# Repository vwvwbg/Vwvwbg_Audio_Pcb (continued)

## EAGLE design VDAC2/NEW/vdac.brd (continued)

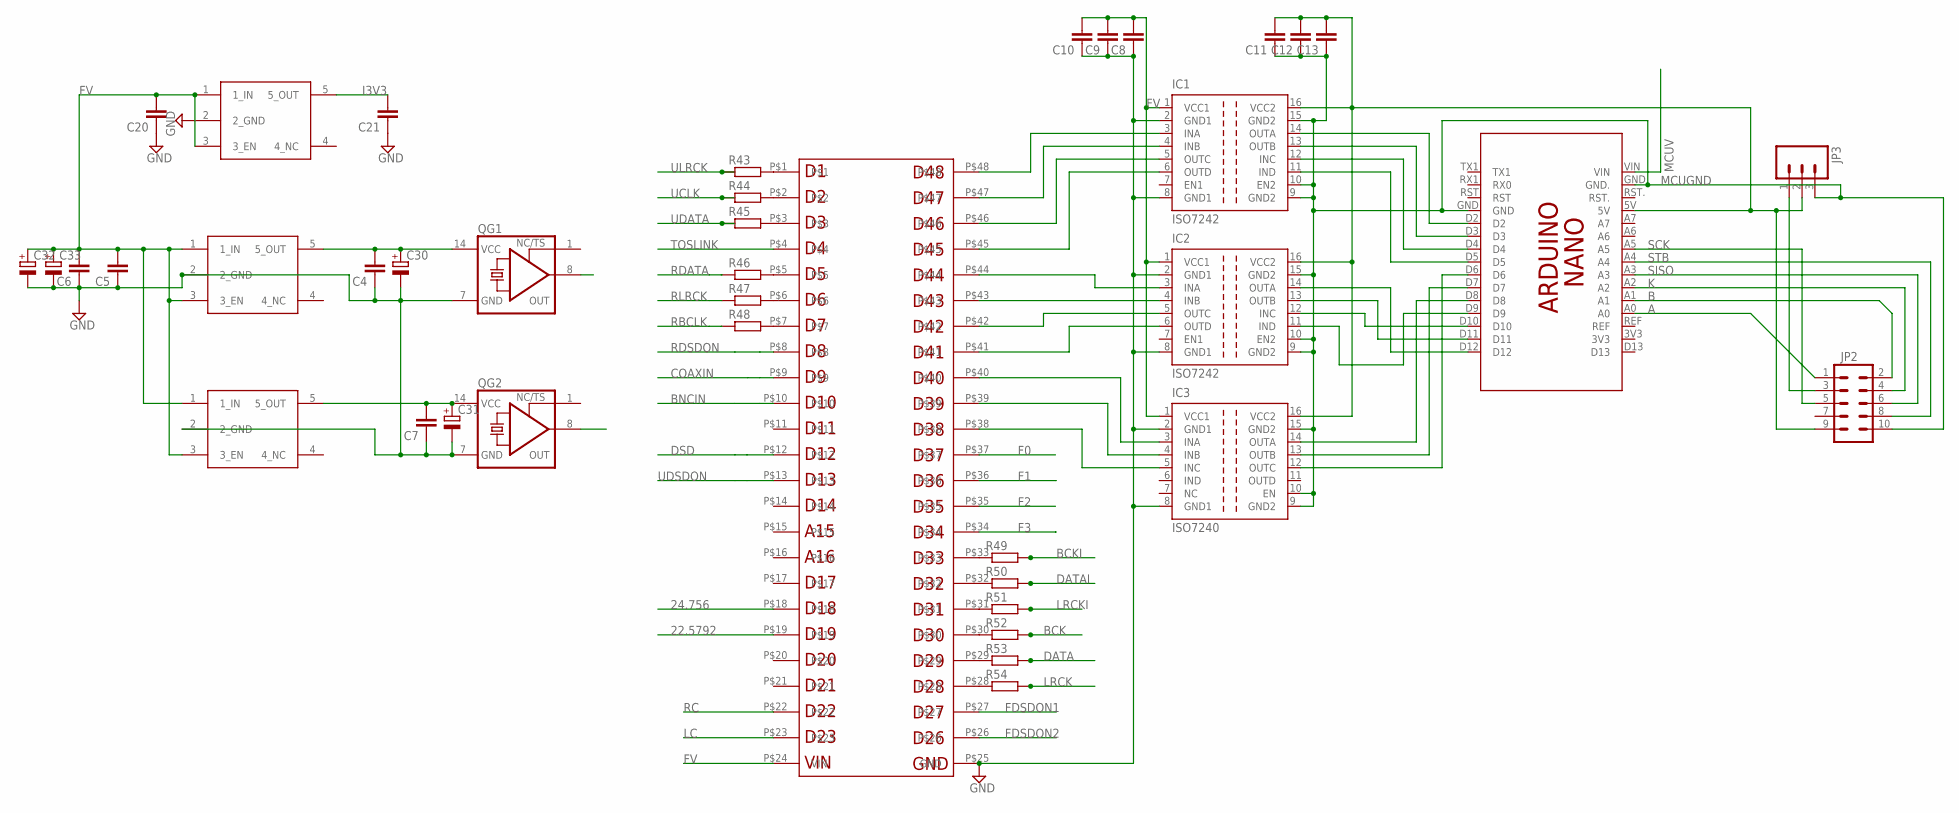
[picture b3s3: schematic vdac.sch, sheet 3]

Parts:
C4, C5, C6, C7, C8, C9, C10, C11, C12, C13, C20, C21: C-EUC0805; C0805
C30, C31, C32, C33: CPOL-EUSP-CAP-CX; SP-CAP-CX
IC1, IC2: ISO7242; SO-16DW
IC3: ISO7240; SO-16DW
JP2: M05X2SHD; 2X5-SHROUDED
JP3: M03JST-PTH-VERT; JST-3-PTH-VERT
PCB1: ARDUINO_NANO
QG1, QG2: XO-14; DIL14S
R43, R44, R45, R46, R47, R48, R49, R50, R51, R52, R53, R54: R-EU_MELF0204W; MINI_MELF-0204W
U$10, U$15, U$16: LP5907; SOT-23-5
U$12: CMOD-A7; CMODA7

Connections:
22.5792: QG2.8 (OUT), U$12.P$19
24.756: QG1.8 (OUT), U$12.P$18
A: JP2.1, PCB1.A0
B: JP2.2, PCB1.A1
BCK: R52.2
BCKI: R49.2; also elsewhere on the board
BNCIN: U$12.P$10; also elsewhere on the board
COAXIN: U$12.P$9; also elsewhere on the board
D2: IC1.14 (OUTA), PCB1.D2
D3: IC1.13 (OUTB), PCB1.D3
D4: IC1.12 (INC), PCB1.D4
D5: IC1.11 (IND), PCB1.D5
DATA: R53.2
DATAI: R50.2; also elsewhere on the board
DSD: U$12.P$12; also elsewhere on the board
F0: U$12.P$37; also elsewhere on the board
F1: U$12.P$36; also elsewhere on the board
F2: U$12.P$35; also elsewhere on the board
F3: U$12.P$34; also elsewhere on the board
FDSDON1: U$12.P$27
FDSDON2: U$12.P$26
FV: C5.2, C6.2, C8.2, C9.2, C10.2, C20.2, C32.+, C33.+, IC1.1 (VCC1), IC2.1 (VCC1), IC3.1 (VCC1), U$10.1 (1_IN), U$10.3 (3_EN), U$12.P$24 (VIN), U$15.1 (1_IN), U$15.3 (3_EN), U$16.1 (1_IN), U$16.3 (3_EN); also elsewhere on the board
GND: C4.1, C5.1, C6.1, C7.1, C8.1, C9.1, C10.1, C20.1, C21.1, C30.-, C31.-, C32.-, C33.-, IC1.2 (GND1), IC1.8 (GND1), IC2.2 (GND1), IC2.8 (GND1), IC3.2 (GND1), IC3.8 (GND1), QG1.7 (GND), QG2.7 (GND), U$10.2 (2_GND), U$12.P$25 (GND), U$15.2 (2_GND), U$16.2 (2_GND); also elsewhere on the board
I3V3: C21.2, U$10.5 (5_OUT); also elsewhere on the board
K: JP2.4, PCB1.A2
LC: U$12.P$23
LRCK: R54.2
LRCKI: R51.2; also elsewhere on the board
MCUGND: C11.1, C12.1, C13.1, IC1.9 (GND2), IC1.10 (EN2), IC1.15 (GND2), IC2.9 (GND2), IC2.10 (EN2), IC2.15 (GND2), IC3.9 (GND2), IC3.10 (EN), IC3.15 (GND2), JP2.10, JP3.3, PCB1.GND, PCB1.GND.; also elsewhere on the board
MCUV: PCB1.VIN; also elsewhere on the board
unnamed: R43.2, U$12.P$1
unnamed: C4.2, C30.+, QG1.14 (VCC), U$15.5 (5_OUT)
unnamed: C7.2, C31.+, QG2.14 (VCC), U$16.5 (5_OUT)
unnamed: IC1.3 (INA), U$12.P$48
unnamed: IC1.4 (INB), U$12.P$47
unnamed: IC1.5 (OUTC), U$12.P$46
unnamed: IC1.6 (OUTD), U$12.P$45
unnamed: IC2.3 (INA), U$12.P$44
unnamed: IC2.4 (INB), U$12.P$43
unnamed: IC2.5 (OUTC), U$12.P$42
unnamed: IC2.6 (OUTD), U$12.P$41
unnamed: IC3.3 (INA), U$12.P$40
unnamed: IC3.4 (INB), U$12.P$39
unnamed: IC3.5 (INC), U$12.P$38
unnamed: IC2.14 (OUTA), PCB1.D12
unnamed: IC2.13 (OUTB), PCB1.D11
unnamed: IC2.12 (INC), PCB1.D10
unnamed: IC2.11 (IND), PCB1.D9
unnamed: IC3.14 (OUTA), PCB1.D8
unnamed: IC3.13 (OUTB), PCB1.D7
unnamed: IC3.12 (OUTC), PCB1.D6
unnamed: C11.2, C12.2, C13.2, IC1.16 (VCC2), IC2.16 (VCC2), IC3.16 (VCC2), JP2.9, JP3.2, PCB1.5V
unnamed: JP2.3, JP3.1
unnamed: R44.2, U$12.P$2
unnamed: R45.2, U$12.P$3
unnamed: R46.2, U$12.P$5
unnamed: R47.2, U$12.P$6
unnamed: R48.2, U$12.P$7
unnamed: R49.1, U$12.P$33
unnamed: R50.1, U$12.P$32
unnamed: R51.1, U$12.P$31
unnamed: R52.1, U$12.P$30
unnamed: R53.1, U$12.P$29
unnamed: R54.1, U$12.P$28
RBCLK: R48.1; also elsewhere on the board
RC: U$12.P$22
RDATA: R46.1; also elsewhere on the board
RDSDON: U$12.P$8; also elsewhere on the board
RLRCK: R47.1; also elsewhere on the board
SCK: JP2.5, PCB1.A5
SISO: JP2.6, PCB1.A3
STB: JP2.8, PCB1.A4
TOSLINK: U$12.P$4; also elsewhere on the board
UCLK: R44.1; also elsewhere on the board
UDATA: R45.1; also elsewhere on the board
UDSDON: U$12.P$13; also elsewhere on the board
ULRCK: R43.1; also elsewhere on the board

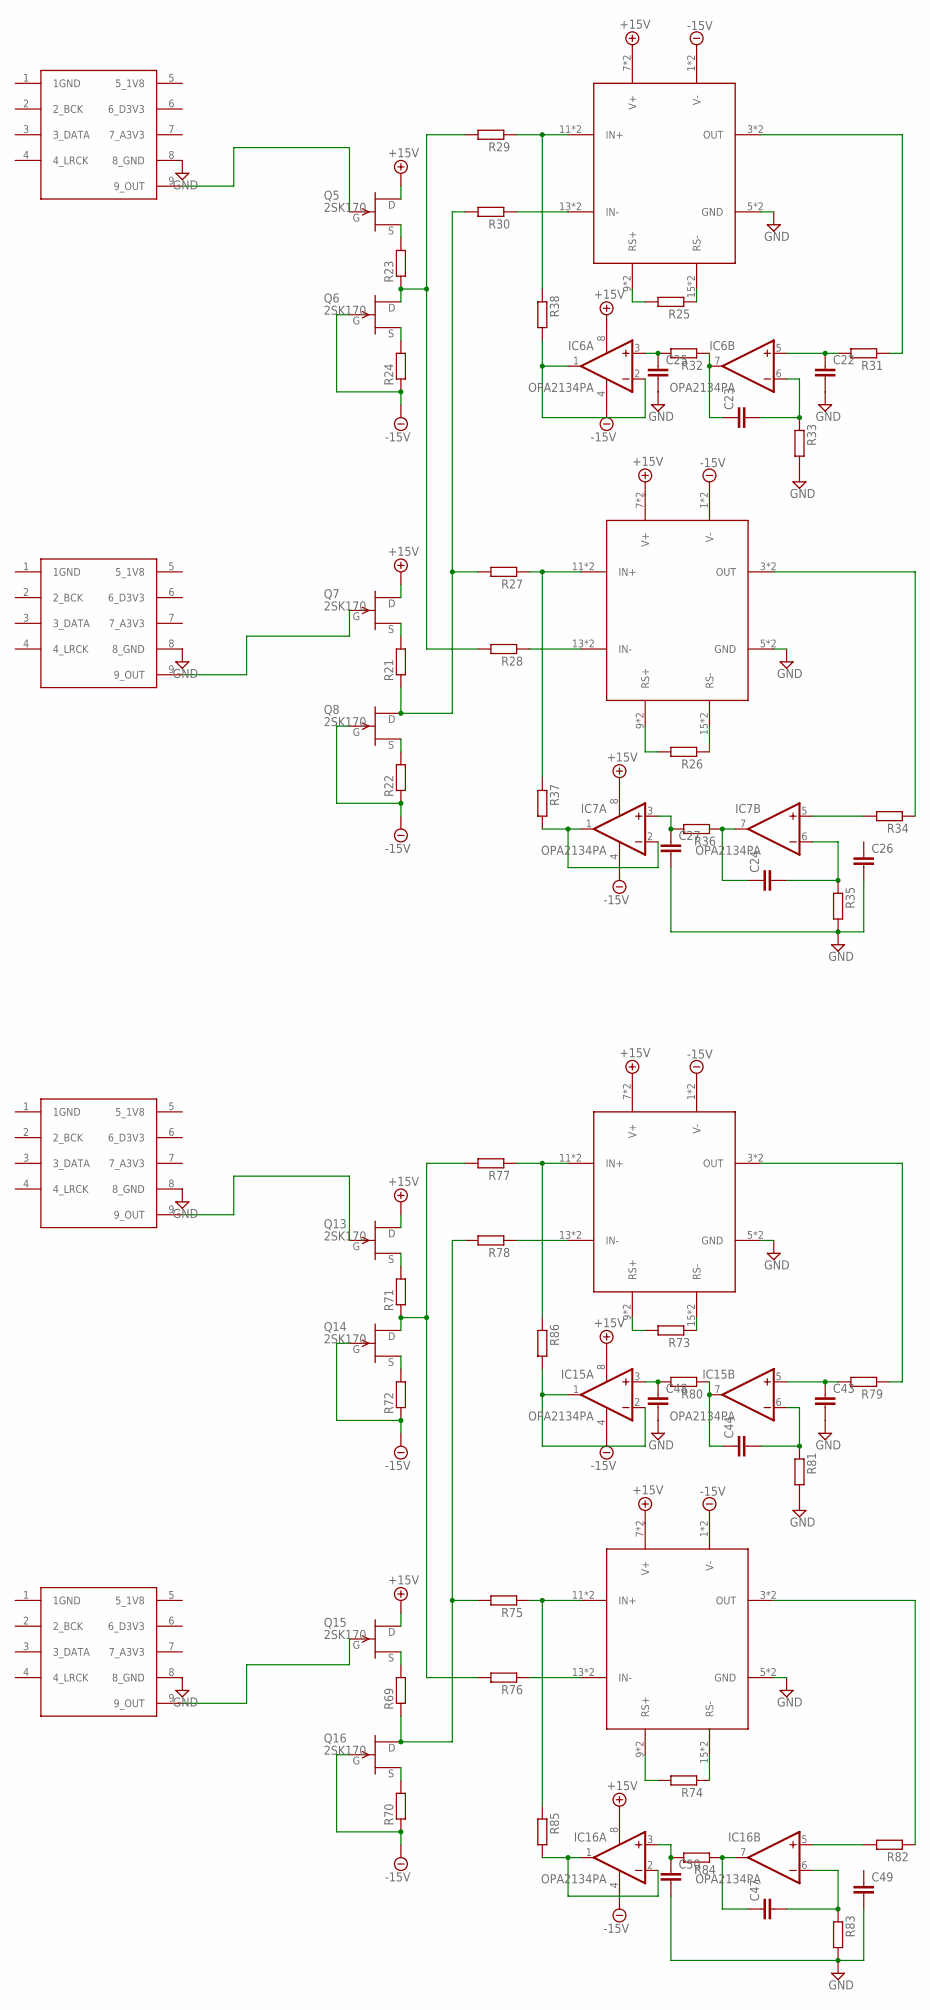
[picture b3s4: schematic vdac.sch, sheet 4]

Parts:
C22, C26, C43, C49: C-EU050-050X075; C050-050X075
C23, C24, C25, C27, C44, C47, C48, C50: C-EU050-035X075; C050-035X075
IC6, IC7, IC15, IC16: OPA2134PA; DIL08
Q5, Q6, Q7, Q8, Q13, Q14, Q15, Q16: 2SK170; TO92-
R21, R22, R23, R24, R25, R26, R27, R28, R29, R30, R31, R32, R33, R34, R35, R36, R37, R38, R69, R70, R71, R72, R73, R74, R75, R76, R77, R78, R79, R80, R81, R82, R83, R84, R85, R86: R-EU_0309/10; 0309/10
U$9, U$11, U$21, U$22: R2R
U$13, U$14, U$23, U$24: 7130MOD

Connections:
+15V: IC6.8 (V+), IC7.8 (V+), IC15.8 (V+), IC16.8 (V+), Q5.1 (D), Q7.1 (D), Q13.1 (D), Q15.1 (D), U$13.7 (V+), U$13.8 (V+), U$14.7 (V+), U$14.8 (V+), U$23.7 (V+), U$23.8 (V+), U$24.7 (V+), U$24.8 (V+); also elsewhere on the board
-15V: IC6.4 (V-), IC7.4 (V-), IC15.4 (V-), IC16.4 (V-), Q6.2 (G), Q8.2 (G), Q14.2 (G), Q16.2 (G), R22.1, R24.1, R70.1, R72.1, U$13.1 (V-), U$13.2 (V-), U$14.1 (V-), U$14.2 (V-), U$23.1 (V-), U$23.2 (V-), U$24.1 (V-), U$24.2 (V-); also elsewhere on the board
GND: C22.2, C25.2, C26.2, C27.2, C43.2, C48.2, C49.2, C50.2, R33.2, R35.2, R81.2, R83.2, U$9.8 (8_GND), U$11.8 (8_GND), U$13.5 (GND), U$13.6 (GND), U$14.5 (GND), U$14.6 (GND), U$21.8 (8_GND), U$22.8 (8_GND), U$23.5 (GND), U$23.6 (GND), U$24.5 (GND), U$24.6 (GND); also elsewhere on the board
unnamed: Q8.3 (S), R22.2
unnamed: Q7.3 (S), R21.2
unnamed: Q6.3 (S), R24.2
unnamed: Q6.1 (D), R23.1, R28.2, R29.2
unnamed: R26.1, U$13.15 (RS-), U$13.16 (RS-)
unnamed: R26.2, U$13.9 (RS+), U$13.10 (RS+)
unnamed: R25.2, U$14.9 (RS+), U$14.10 (RS+)
unnamed: R25.1, U$14.15 (RS-), U$14.16 (RS-)
unnamed: Q5.3 (S), R23.2
unnamed: Q8.1 (D), R21.1, R27.2, R30.2
unnamed: Q7.2 (G), U$11.9 (9_OUT)
unnamed: Q5.2 (G), U$9.9 (9_OUT)
unnamed: R27.1, R37.1, U$13.11 (IN+), U$13.12 (IN+)
unnamed: R28.1, U$13.13 (IN-), U$13.14 (IN-)
unnamed: R29.1, R38.1, U$14.11 (IN+), U$14.12 (IN+)
unnamed: R30.1, U$14.13 (IN-), U$14.14 (IN-)
unnamed: C22.1, IC6.5 (+IN), R31.2
unnamed: R31.1, U$14.3 (OUT), U$14.4 (OUT)
unnamed: IC7.1 (OUT), IC7.2 (-IN), R37.2
unnamed: IC6.1 (OUT), IC6.2 (-IN), R38.2
unnamed: C24.1, IC7.7 (OUT), R36.1
unnamed: C24.2, IC7.6 (-IN), R35.1
unnamed: C23.1, IC6.7 (OUT), R32.1
unnamed: C25.1, IC6.3 (+IN), R32.2
unnamed: C23.2, IC6.6 (-IN), R33.1
unnamed: C27.1, IC7.3 (+IN), R36.2
unnamed: IC7.5 (+IN), R34.2
unnamed: R34.1, U$13.3 (OUT), U$13.4 (OUT)
unnamed: Q16.3 (S), R70.2
unnamed: Q15.3 (S), R69.2
unnamed: Q14.3 (S), R72.2
unnamed: Q14.1 (D), R71.1, R76.2, R77.2
unnamed: R74.1, U$23.15 (RS-), U$23.16 (RS-)
unnamed: R74.2, U$23.9 (RS+), U$23.10 (RS+)
unnamed: R73.2, U$24.9 (RS+), U$24.10 (RS+)
unnamed: R73.1, U$24.15 (RS-), U$24.16 (RS-)
unnamed: Q13.3 (S), R71.2
unnamed: Q16.1 (D), R69.1, R75.2, R78.2
unnamed: Q15.2 (G), U$22.9 (9_OUT)
unnamed: Q13.2 (G), U$21.9 (9_OUT)
unnamed: R75.1, R85.1, U$23.11 (IN+), U$23.12 (IN+)
unnamed: R76.1, U$23.13 (IN-), U$23.14 (IN-)
unnamed: R77.1, R86.1, U$24.11 (IN+), U$24.12 (IN+)
unnamed: R78.1, U$24.13 (IN-), U$24.14 (IN-)
unnamed: C43.1, IC15.5 (+IN), R79.2
unnamed: R79.1, U$24.3 (OUT), U$24.4 (OUT)
unnamed: IC16.1 (OUT), IC16.2 (-IN), R85.2
unnamed: IC15.1 (OUT), IC15.2 (-IN), R86.2
unnamed: C47.1, IC16.7 (OUT), R84.1
unnamed: C47.2, IC16.6 (-IN), R83.1
unnamed: C44.1, IC15.7 (OUT), R80.1
unnamed: C48.1, IC15.3 (+IN), R80.2
unnamed: C44.2, IC15.6 (-IN), R81.1
unnamed: C50.1, IC16.3 (+IN), R84.2
unnamed: IC16.5 (+IN), R82.2
unnamed: R82.1, U$23.3 (OUT), U$23.4 (OUT)

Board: 2 copper layers, 167 parts (31 on the bottom side), 155 nets, no tracks yet.

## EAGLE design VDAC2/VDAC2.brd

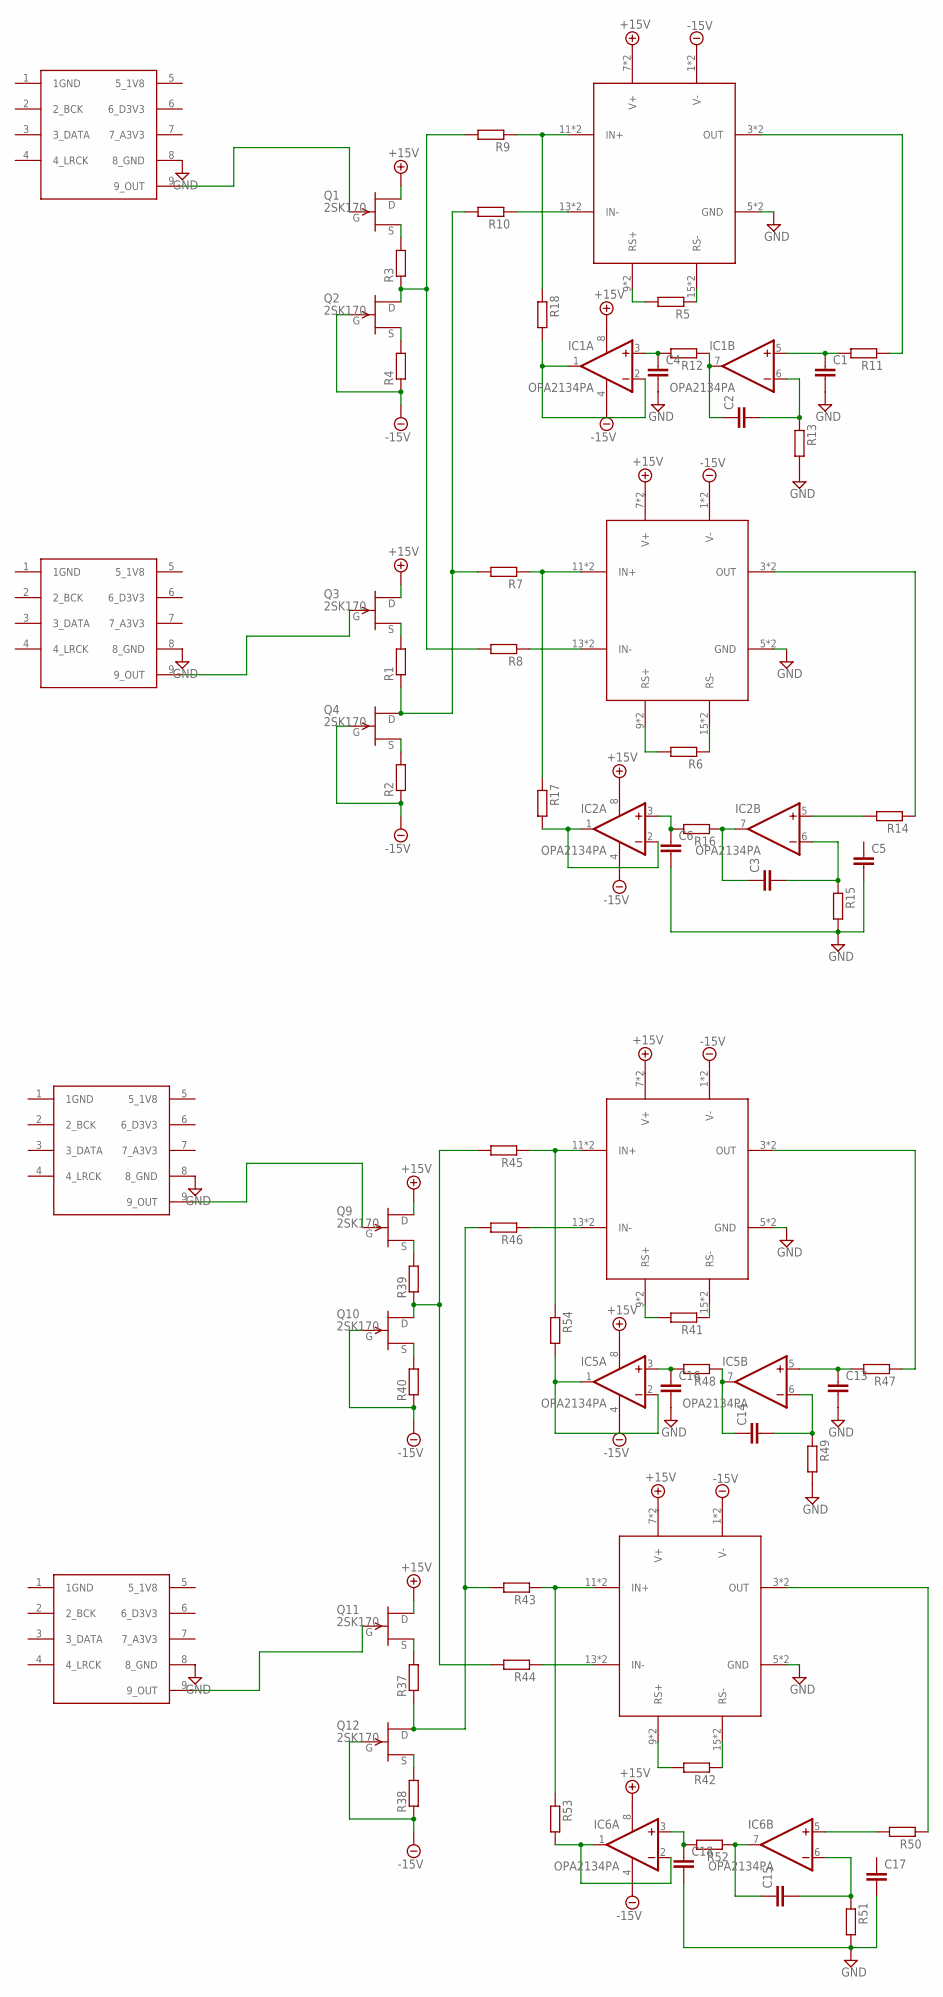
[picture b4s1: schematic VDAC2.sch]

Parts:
C1, C5, C13, C17: C-EU050-050X075; C050-050X075
C2, C3, C4, C6, C14, C15, C16, C18: C-EU050-035X075; C050-035X075
IC1, IC2, IC5, IC6: OPA2134PA; DIL08
Q1, Q2, Q3, Q4, Q9, Q10, Q11, Q12: 2SK170; TO92-
R1, R2, R3, R4, R5, R6, R7, R8, R9, R10, R11, R12, R13, R14, R15, R16, R17, R18, R37, R38, R39, R40, R41, R42, R43, R44, R45, R46, R47, R48, R49, R50, R51, R52, R53, R54: R-EU_0309/10; 0309/10
U$1, U$2, U$11, U$12: 7130MOD
U$5, U$6, U$9, U$10: R2R

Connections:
+15V: IC1.8 (V+), IC2.8 (V+), IC5.8 (V+), IC6.8 (V+), Q1.1 (D), Q3.1 (D), Q9.1 (D), Q11.1 (D), U$1.7 (V+), U$1.8 (V+), U$2.7 (V+), U$2.8 (V+), U$11.7 (V+), U$11.8 (V+), U$12.7 (V+), U$12.8 (V+)
-15V: IC1.4 (V-), IC2.4 (V-), IC5.4 (V-), IC6.4 (V-), Q2.2 (G), Q4.2 (G), Q10.2 (G), Q12.2 (G), R2.1, R4.1, R38.1, R40.1, U$1.1 (V-), U$1.2 (V-), U$2.1 (V-), U$2.2 (V-), U$11.1 (V-), U$11.2 (V-), U$12.1 (V-), U$12.2 (V-)
GND: C1.2, C4.2, C5.2, C6.2, C13.2, C16.2, C17.2, C18.2, R13.2, R15.2, R49.2, R51.2, U$1.5 (GND), U$1.6 (GND), U$2.5 (GND), U$2.6 (GND), U$5.8 (8_GND), U$6.8 (8_GND), U$9.8 (8_GND), U$10.8 (8_GND), U$11.5 (GND), U$11.6 (GND), U$12.5 (GND), U$12.6 (GND)
unnamed: Q4.3 (S), R2.2
unnamed: R7.1, R17.1, U$1.11 (IN+), U$1.12 (IN+)
unnamed: R9.1, R18.1, U$2.11 (IN+), U$2.12 (IN+)
unnamed: Q3.3 (S), R1.2
unnamed: Q2.3 (S), R4.2
unnamed: R8.1, U$1.13 (IN-), U$1.14 (IN-)
unnamed: Q2.1 (D), R3.1, R8.2, R9.2
unnamed: Q4.1 (D), R1.1, R7.2, R10.2
unnamed: R6.1, U$1.15 (RS-), U$1.16 (RS-)
unnamed: R6.2, U$1.9 (RS+), U$1.10 (RS+)
unnamed: R5.2, U$2.9 (RS+), U$2.10 (RS+)
unnamed: R5.1, U$2.15 (RS-), U$2.16 (RS-)
unnamed: Q1.3 (S), R3.2
unnamed: R10.1, U$2.13 (IN-), U$2.14 (IN-)
unnamed: Q3.2 (G), U$6.9 (9_OUT)
unnamed: Q1.2 (G), U$5.9 (9_OUT)
unnamed: C1.1, IC1.5 (+IN), R11.2
unnamed: R11.1, U$2.3 (OUT), U$2.4 (OUT)
unnamed: IC2.1 (OUT), IC2.2 (-IN), R17.2
unnamed: IC1.1 (OUT), IC1.2 (-IN), R18.2
unnamed: C3.1, IC2.7 (OUT), R16.1
unnamed: C3.2, IC2.6 (-IN), R15.1
unnamed: C2.2, IC1.6 (-IN), R13.1
unnamed: C2.1, IC1.7 (OUT), R12.1
unnamed: C4.1, IC1.3 (+IN), R12.2
unnamed: C6.1, IC2.3 (+IN), R16.2
unnamed: IC2.5 (+IN), R14.2
unnamed: R14.1, U$1.3 (OUT), U$1.4 (OUT)
unnamed: Q12.3 (S), R38.2
unnamed: Q11.3 (S), R37.2
unnamed: Q10.3 (S), R40.2
unnamed: Q10.1 (D), R39.1, R44.2, R45.2
unnamed: R42.1, U$11.15 (RS-), U$11.16 (RS-)
unnamed: R42.2, U$11.9 (RS+), U$11.10 (RS+)
unnamed: R41.2, U$12.9 (RS+), U$12.10 (RS+)
unnamed: R41.1, U$12.15 (RS-), U$12.16 (RS-)
unnamed: Q9.3 (S), R39.2
unnamed: Q12.1 (D), R37.1, R43.2, R46.2
unnamed: Q11.2 (G), U$10.9 (9_OUT)
unnamed: Q9.2 (G), U$9.9 (9_OUT)
unnamed: R43.1, R53.1, U$11.11 (IN+), U$11.12 (IN+)
unnamed: R44.1, U$11.13 (IN-), U$11.14 (IN-)
unnamed: R45.1, R54.1, U$12.11 (IN+), U$12.12 (IN+)
unnamed: R46.1, U$12.13 (IN-), U$12.14 (IN-)
unnamed: C13.1, IC5.5 (+IN), R47.2
unnamed: R47.1, U$12.3 (OUT), U$12.4 (OUT)
unnamed: IC6.1 (OUT), IC6.2 (-IN), R53.2
unnamed: IC5.1 (OUT), IC5.2 (-IN), R54.2
unnamed: C15.1, IC6.7 (OUT), R52.1
unnamed: C15.2, IC6.6 (-IN), R51.1
unnamed: C14.1, IC5.7 (OUT), R48.1
unnamed: C16.1, IC5.3 (+IN), R48.2
unnamed: C14.2, IC5.6 (-IN), R49.1
unnamed: C18.1, IC6.3 (+IN), R52.2
unnamed: IC6.5 (+IN), R50.2
unnamed: R50.1, U$11.3 (OUT), U$11.4 (OUT)

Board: 2 copper layers, 68 parts (0 on the bottom side), 59 nets, no tracks yet.

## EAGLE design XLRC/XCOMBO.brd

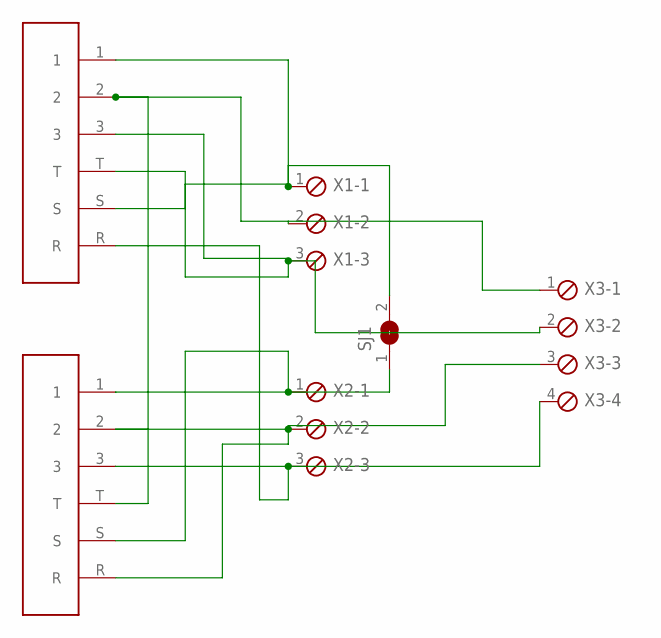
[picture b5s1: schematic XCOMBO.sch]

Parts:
SJ1: SJ
U$1, U$2: XLRCOMBO; NCJ6FI-S-0
X1, X2: MPT3; 3POL254
X3: MPT4; 4POL254

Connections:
L+: U$1.T, U$2.2, X1.2, X3.1
L-: U$2.3, U$2.T, X1.3, X3.2
LG: SJ1.2, U$2.1, U$2.S, X1.1
R+: U$1.2, U$1.R, X2.2, X3.3
R-: U$1.3, U$2.R, X2.3, X3.4
RG: SJ1.1, U$1.1, U$1.S, X2.1

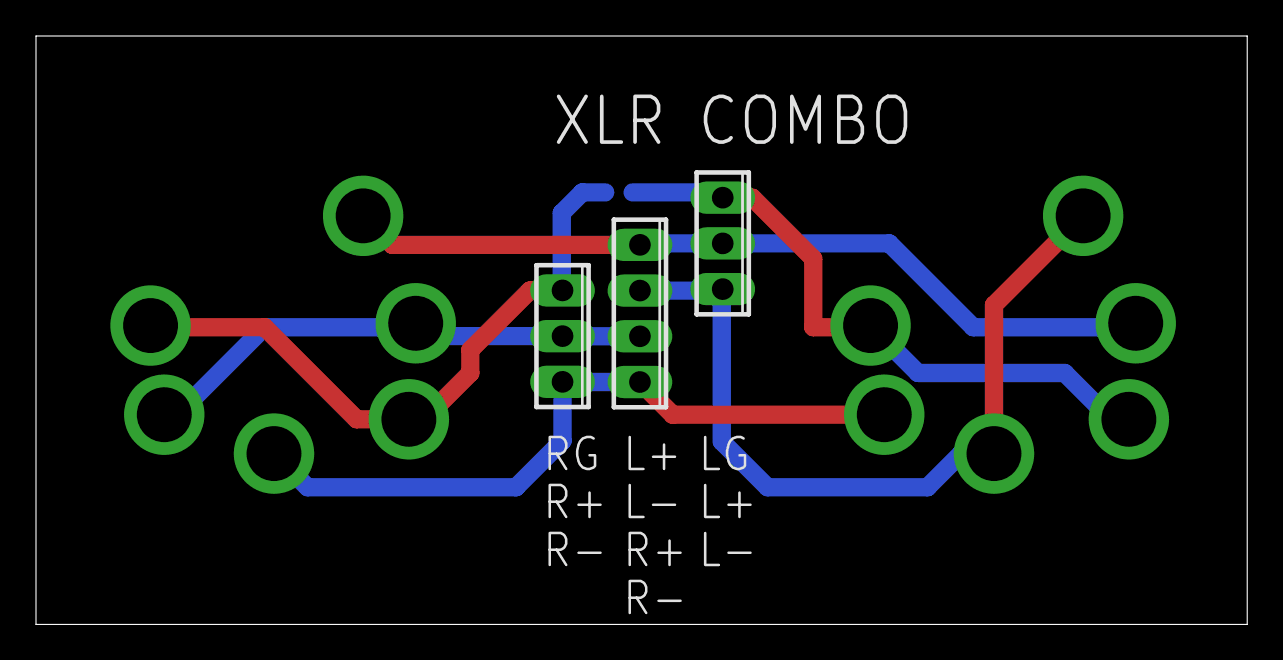
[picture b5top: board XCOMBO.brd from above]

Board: 2 copper layers, 67.3 x 32.7 mm, 6 parts (1 on the bottom side), 6 nets.
